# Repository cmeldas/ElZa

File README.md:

# ElZa
Elektronické zapalování

Pokus o elektronické zapalování.

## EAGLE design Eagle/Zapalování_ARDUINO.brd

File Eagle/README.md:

## Eagle files

navrženo v EAGLE 7.5 lite

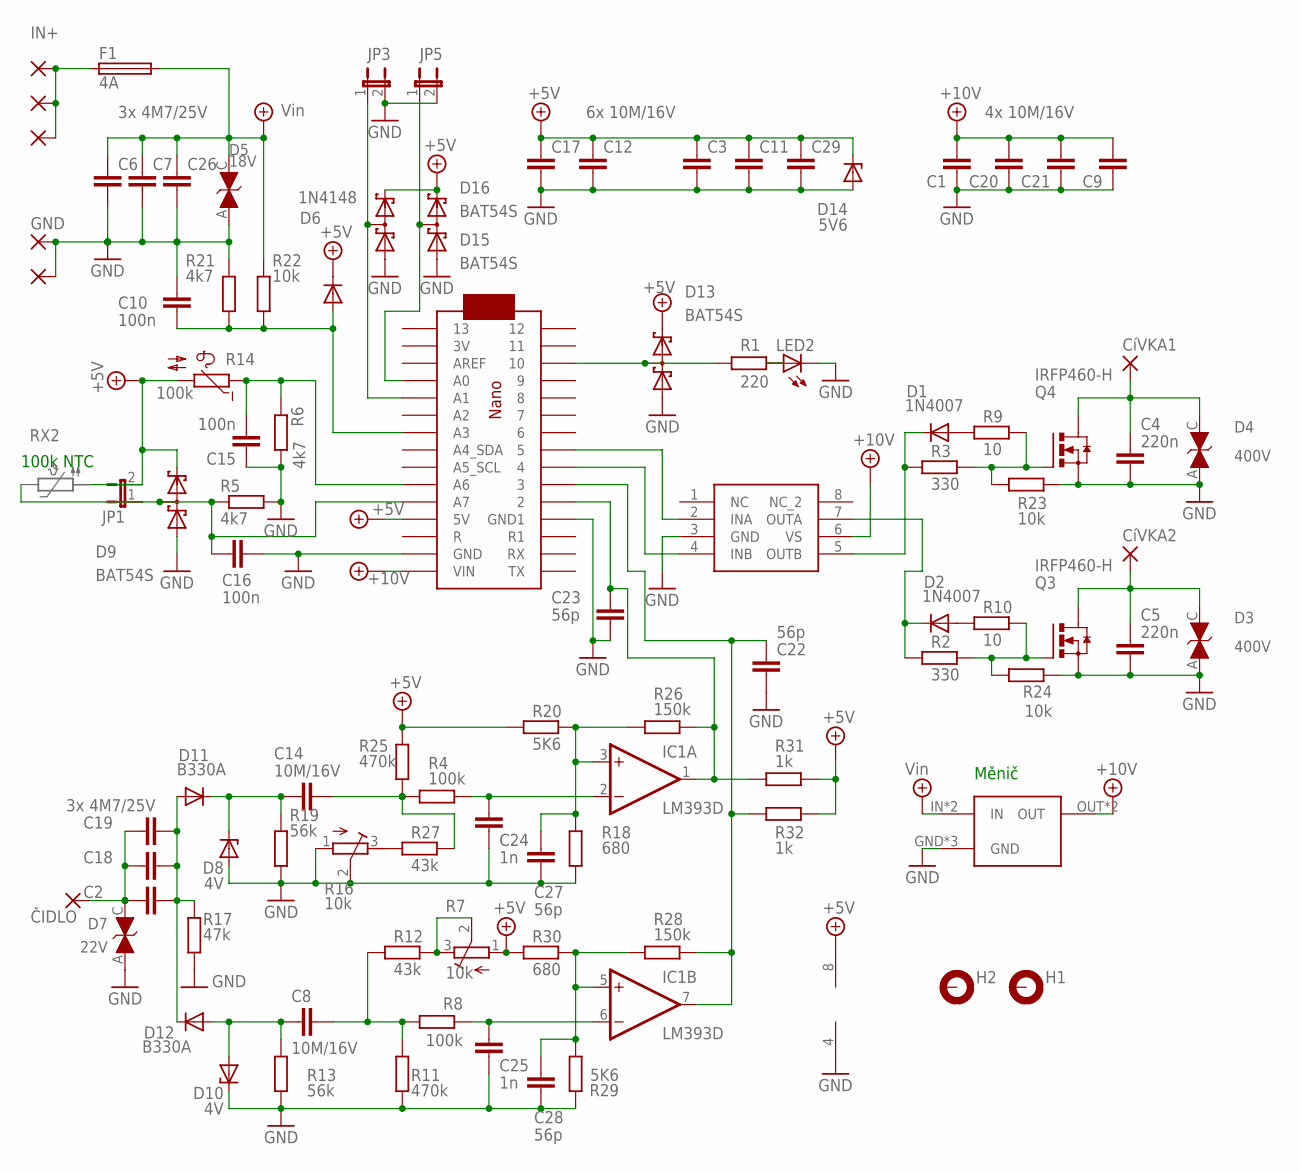
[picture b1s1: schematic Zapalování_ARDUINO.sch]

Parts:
C1, C8, C9, C11, C12, C14, C17, C20, C29: 10M/16V; C1206K
C2, C26: 3x 4M7/25V; C1206K
C3: 6x 10M/16V; C1206K
C4, C5: 220n; C150-054X183
C6, C7, C18, C19: 4M7/25V; C1206K
C10, C15, C16: 100n; C1206K
C21: 4x 10M/16V; C1206K
C22, C23, C27, C28: 56p; C1206K
C24, C25: 1n; C1206K
CIVKA+: 3,81/1,4
CíVKA1, CíVKA2: 3,81/1,4
CíVKA+: 3,81/1,4
D1, D2: 1N4007; SMA-DO214AC
D3, D4: 400V; SMC
D5: 18V; SMC
D6: 1N4148; SOD80C
D7: 22V; SMC
D8, D10: 4V; SOD80C
D9, D13, D15, D16: BAT54S; SOT23
D11, D12: B330A; DO214BA
D14: 5V6; SOD80C
F1: 4A; PICOFUSE
GND, GND28: 3,81/1,4
H1, H2: MOUNT-PAD-ROUND3.0; 3,0-PAD
IC1: LM393D; SO08
IN+: 3,81/1,4
JP1, JP3, JP5: JP1E; JP1
LED2: LED5MM
Q3, Q4: IRFP460-H; TO247BH
R1: 220; M1206
R2, R3: 330; M1206
R4, R8: 100k; M1206
R5, R6, R21: 4k7; M1206
R7, R16: 10k; RTRIM64W
R9, R10: 10; M1206
R11, R25: 470k; M1206
R12, R27: 43k; M1206
R13, R19: 56k; M1206
R14: 100k; N640
R17: 47k; M1206
R18, R30: 680; M1206
R20, R29: 5K6; M1206
R22, R23, R24: 10k; M1206
R26, R28: 150k; M1206
R31, R32: 1k; M1206
U$1: ARDUINO_NANO
U$2: IR25600/TC4427; SO08
U$3: STEP:DOWN; STEP-BOARD
ČIDLO: 3,81/1,4

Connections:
+5V: C3.1, C11.1, C12.1, C17.1, C29.1, D6.C, D9.2 (C2), D13.2 (C2), D14.C, D15.2 (C2), D16.2 (C2), IC1.8 (V+), JP1.2, R7.1 (A), R14.2, R20.2, R25.2, R30.2, R31.1, R32.1, U$1.P$23 (5V)
+14V: C6.1, C7.1, C26.1, D5.C, F1.2, R22.2, U$3.IN, U$3.P$1 (IN)
+15V: C1.2, C9.1, C20.2, C21.2, U$1.P$20 (VIN), U$2.6 (VS), U$3.OUT, U$3.P$2 (OUT)
CIVKA1: U$1.P$8 (5), U$2.2 (INA)
CIVKA2: U$1.P$9 (4), U$2.4 (INB)
GND: C1.1, C3.2, C4.2, C5.2, C6.2, C7.2, C9.2, C10.1, C11.2, C12.2, C15.1, C16.1, C17.2, C20.1, C21.1, C22.2, C23.2, C24.2, C25.2, C26.2, C27.2, C28.2, C29.2, D3.A, D4.A, D5.A, D7.A, D8.A, D9.1 (A1), D10.C, D13.1 (A1), D14.A, D15.1 (A1), D16.1 (A1), GND.1, GND28.1, IC1.4 (V-), JP3.2, JP5.2, LED2.K (C), Q3.S, Q4.S, R5.2, R6.2, R11.1, R13.1, R16.1 (A), R16.2 (S), R17.1, R18.1, R19.1, R21.2, R23.1, R24.1, R29.2, U$1.P$12 (GND), U$1.P$21 (GND1), U$2.3 (GND), U$3.GND, U$3.GND2 (GND), U$3.P$3 (GND)
INT1: C23.1, IC1.1 (OUT), R26.1, R31.2, U$1.P$11 (2)
INT2: C22.1, IC1.7 (OUT), R28.1, R32.2, U$1.P$10 (3)
unnamed: Q4.G, R3.2, R9.2, R23.2
unnamed: D1.K (C), R3.1, U$2.5 (OUTB)
unnamed: C4.1, CíVKA1.1, D4.C, Q4.D
unnamed: Q3.G, R2.2, R10.2, R24.2
unnamed: D2.K (C), R2.1, U$2.7 (OUTA)
unnamed: D15.3 (C1A2), JP3.1, U$1.P$30 (A1)
unnamed: D16.3 (C1A2), JP5.1, U$1.P$31 (A0)
unnamed: D13.3 (C1A2), R1.2, U$1.P$3 (10)
unnamed: C16.2, D9.3 (C1A2), JP1.1, R5.1, U$1.P$24 (A7)
unnamed: C28.1, IC1.5 (+IN), R28.2, R29.1, R30.1
unnamed: C24.1, IC1.2 (-IN), R4.1
unnamed: LED2.A, R1.1
unnamed: C27.1, IC1.3 (+IN), R18.2, R20.1, R26.2
unnamed: C2.2, C18.2, C19.2, D7.C, ČIDLO.1
unnamed: C14.2, D8.C, D11.C, R19.2
unnamed: C15.2, R6.1, R14.1, U$1.P$25 (A6)
unnamed: C2.1, C18.1, C19.1, D11.A, D12.C, R17.2
unnamed: C25.1, IC1.6 (-IN), R8.1
unnamed: R7.2 (S), R7.3 (E), R12.1
unnamed: C8.1, R8.2, R11.2, R12.2
unnamed: R16.3 (E), R27.2
unnamed: C8.2, D10.A, D12.A, R13.2
unnamed: D2.A, R10.1
unnamed: D1.A, R9.1
unnamed: C5.1, CíVKA2.1, D3.C, Q3.D
unnamed: C14.1, R4.2, R25.1, R27.1
unnamed: C10.2, D6.A, R21.1, R22.1, U$1.P$28 (A3)
VIN: CIVKA+.1, CíVKA+.1, F1.1, IN+.1

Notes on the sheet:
100k NTC
Měnič

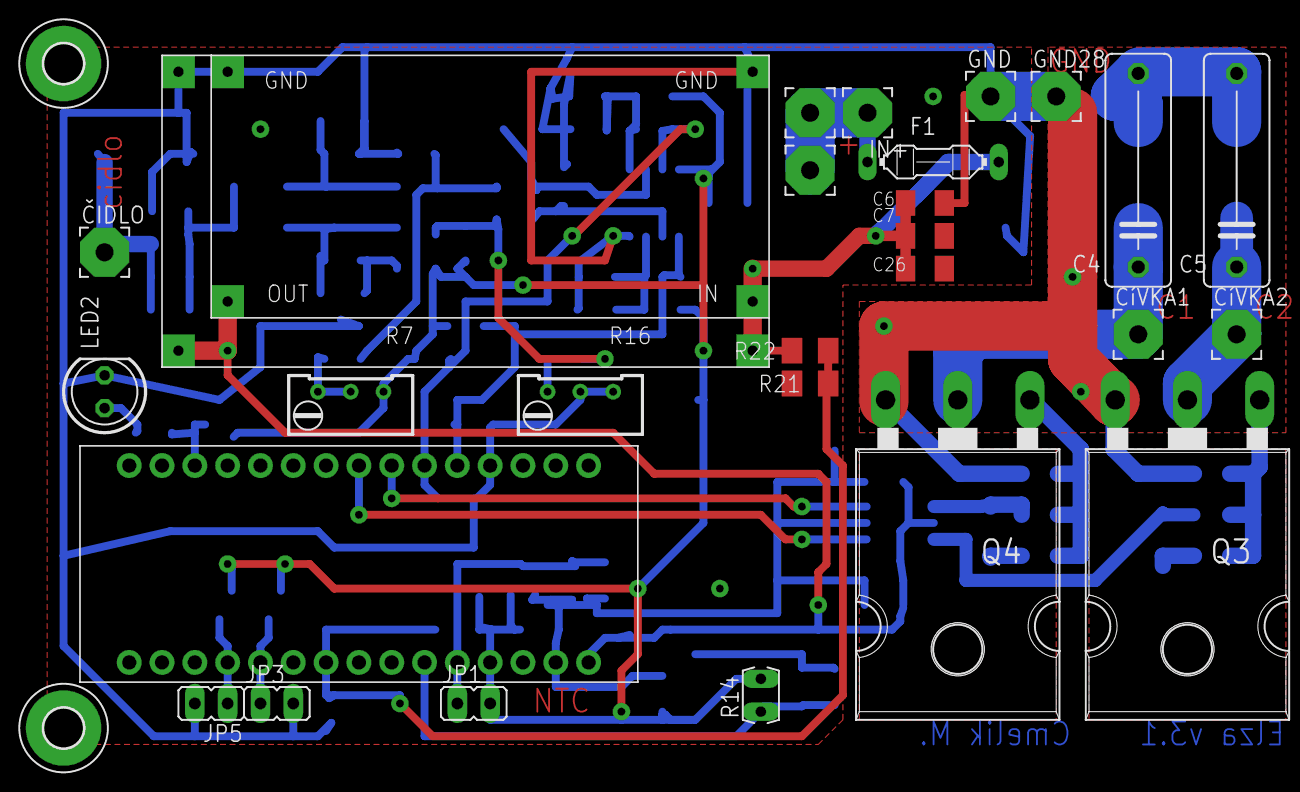
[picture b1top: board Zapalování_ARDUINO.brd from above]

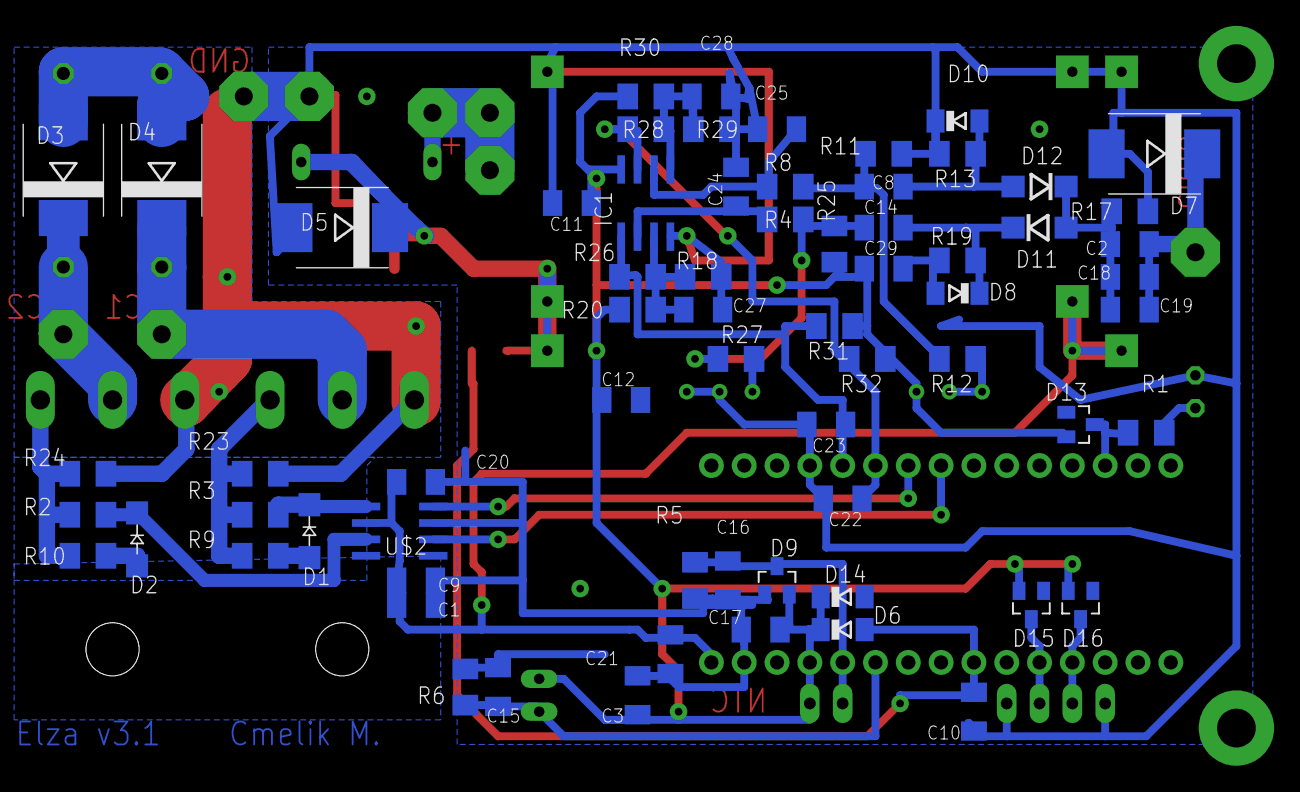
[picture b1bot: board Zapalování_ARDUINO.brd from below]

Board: 2 copper layers, 96 parts (67 on the bottom side), 36 nets.

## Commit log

2016-06-01 Create gh-pages branch via GitHub
2016-06-01 Create PCB
2016-06-01 Create program
